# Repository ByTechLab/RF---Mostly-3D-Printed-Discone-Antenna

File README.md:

<div align="center">
    
</div>

Mostly 3D printed discone antenna for Software Definied Radio.

### Read more at BYTECHLAB:

<table style="width: 100%; border: none;" cellspacing="0" cellpadding="0" border="0">
  <tr>
    <td></td>
    <td>https://bytechlab.com/2018/05/mostly-3d-printed-discone-antenna/</td>
  </tr>
</table>

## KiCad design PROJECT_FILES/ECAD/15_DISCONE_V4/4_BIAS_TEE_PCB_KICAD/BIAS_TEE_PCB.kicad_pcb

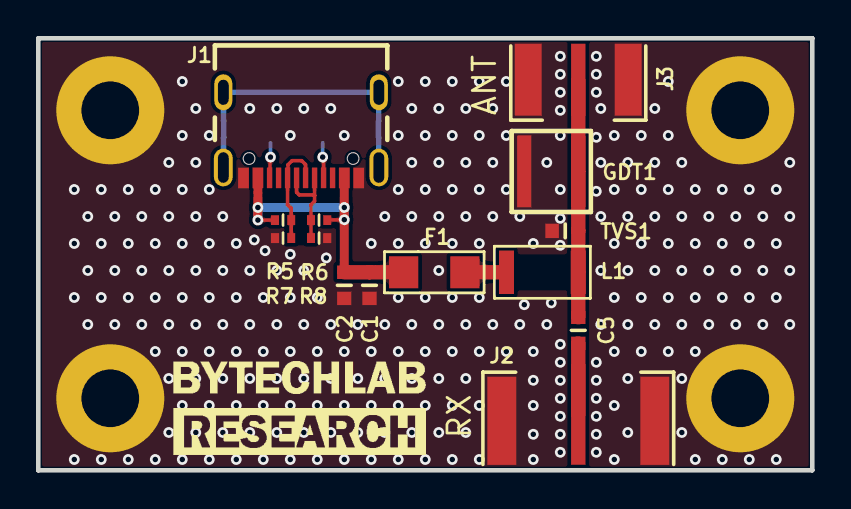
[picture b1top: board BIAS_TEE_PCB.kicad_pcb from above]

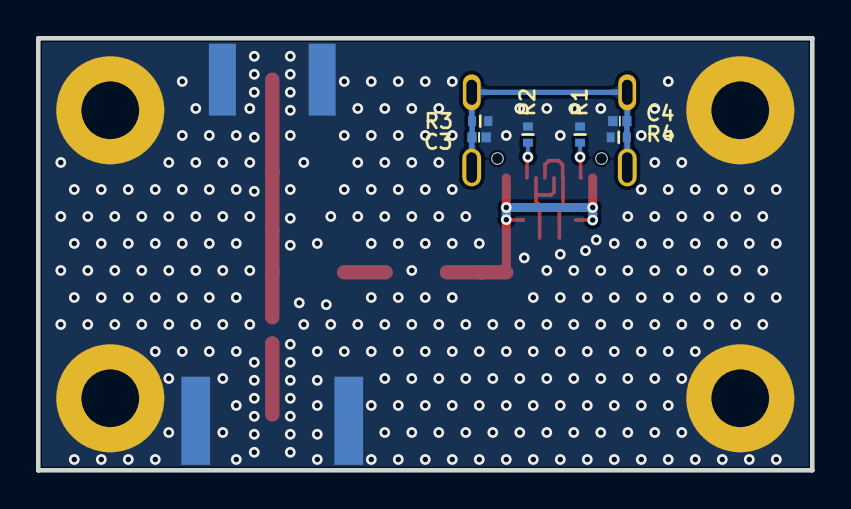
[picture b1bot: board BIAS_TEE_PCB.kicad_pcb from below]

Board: 2 copper layers, 43.0 x 24.0 mm, 20 parts (6 on the bottom side), 10 nets.

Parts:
C1: 100n; C_0603_1608
C2: 1u; C_0603_1608
C3, C4: 100n; C_0402_1005
C5: 10n; C_0603_1608
F1: F_250mA_24V_1206
GDT1: GDT_CG775MS
J1: J_USB_C_USB4105
J2: J_132366
J3: J_RF2-143-T-17-50-G
L1: 5.6uH; L_RF_5.6uH_4.4x2mm_WA8514-AE
R1, R2: 5.1k; R_0402_1005
R3, R4: 1M; R_0402_1005
R5, R6, R7, R8: NC; R_NC_0402_1005
TVS1: R_0603_1608

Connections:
GND: C1.2, C2.2, C3.2, C4.2, GDT1.2, J1.AB112 (GND), J1.BA112 (GND), J2.2 (GND), J3.2 (GND), R1.1, R2.1, R3.1, R4.1, R7.1, R8.1, TVS1.2
unnamed: C3.1, C4.1, J1.MH (GND), R3.2, R4.2
unnamed: F1.2, L1.2
unnamed: J1.A5 (CC1), R2.2
unnamed: J1.B5 (CC2), R1.2
unnamed: J1.A6 (D1+), J1.B6 (D2+), R5.1, R7.2
unnamed: J1.A7 (D1-), J1.B7 (D2-), R6.1, R8.2
unnamed: C5.2, J2.1 (X)
unnamed: C5.1, GDT1.1, J3.1 (X), L1.1, TVS1.1
VBUS: C1.1, C2.1, F1.1, J1.AB49 (VBUS), J1.BA49 (VBUS), R5.2, R6.2

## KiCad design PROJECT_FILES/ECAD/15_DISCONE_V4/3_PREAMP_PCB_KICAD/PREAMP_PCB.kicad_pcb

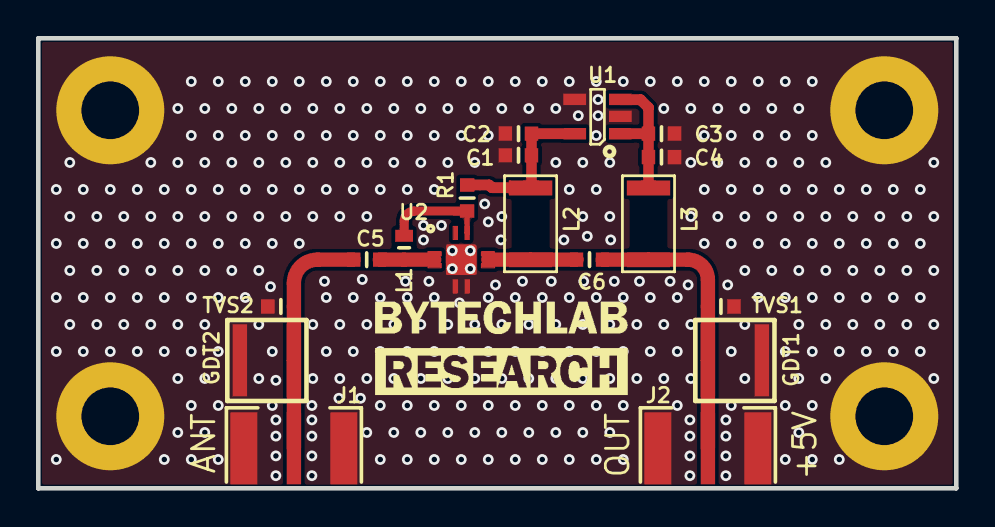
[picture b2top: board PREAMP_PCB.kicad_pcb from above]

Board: 2 copper layers, 51.0 x 25.0 mm, 18 parts (0 on the bottom side), 8 nets.

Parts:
C1, C4: 1u; C_0603_1608
C2, C3: 100n; C_0603_1608
C5, C6: 10n; C_0603_1608
GDT1, GDT2: GDT_CG775MS
J1, J2: J_RF2-143-T-17-50-G
L1: 390nH; L_RF_390nH_0603_LQW18ANR39J00D
L2, L3: 5.6uH; L_RF_5.6uH_4.4x2mm_WA8514-AE
R1: 1k; R_0603_1608
TVS1, TVS2: R_0603_1608
U1: VL_NCV8163ASN300T1G
U2: U_PMA-5452+

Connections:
GND: C1.2, C2.2, C3.2, C4.2, GDT1.2, GDT2.2, J1.2 (GND), J2.2 (GND), TVS1.2, TVS2.2, U1.2 (GND), U1.4 (NC), U2.3 (NC_2), U2.4 (NC_3), U2.EP1 (GND)
unnamed: C5.1, GDT2.1, J1.1 (X), TVS2.1
unnamed: C6.2, GDT1.1, J2.1 (X), L3.1, TVS1.1
unnamed: C3.1, C4.1, L3.2, U1.1 (IN), U1.3 (EN)
unnamed: C1.1, C2.1, L2.2, R1.2, U1.5 (OUT)
unnamed: L1.2, R1.1, U2.7 (BIAS)
unnamed: C5.2, L1.1, U2.1 (RF-IN), U2.2 (NC_1)
unnamed: C6.1, L2.1, U2.5 (NC_4), U2.6 (RF-OUT&DC)

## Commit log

2025-08-10 Uplaod files
2025-08-13 Update jobset & exported files
2025-08-17 Upload files
